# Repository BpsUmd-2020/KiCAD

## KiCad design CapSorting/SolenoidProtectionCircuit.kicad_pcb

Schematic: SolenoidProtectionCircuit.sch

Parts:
D1, D12: 1N4003; D_DO-41_SOD81_P10.16mm_Horizontal
J11: Conn_01x06; JST_XH_S6B-XH-A_1x06_P2.50mm_Horizontal
Q1, Q12: 2SA1015; TO-92_Inline
Q2, Q13: IRLB8721PBF; IRLB8721PBF-2
R1, R3, R12, R14: 10k; R_0603_1608Metric
R2, R13: 47k; R_0603_1608Metric
R4, R15: 22k; R_0603_1608Metric

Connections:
+24V: D1.1, D12.1, J11.6, Q1.1, Q12.1, R2.1, R13.1
GND: J11.1, Q2.3, Q13.3, R4.2, R15.2
unnamed: Q1.2, R3.2
unnamed: Q1.3, R1.1, R2.2
unnamed: Q2.1, R3.1, R4.1
unnamed: Q12.2, R14.2
unnamed: Q12.3, R12.1, R13.2
unnamed: Q13.1, R14.1, R15.1
PLC_Y006: J11.3, R12.2
PLC_Y012: J11.5, R1.2
Solenoid1: D12.2, J11.2, Q13.2
Solenoid2: D1.2, J11.4, Q2.2

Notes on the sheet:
Solenoid protection
Vgs:16.5V
Vds:30V Pd:65W(temp=25) 33W(temp=100)

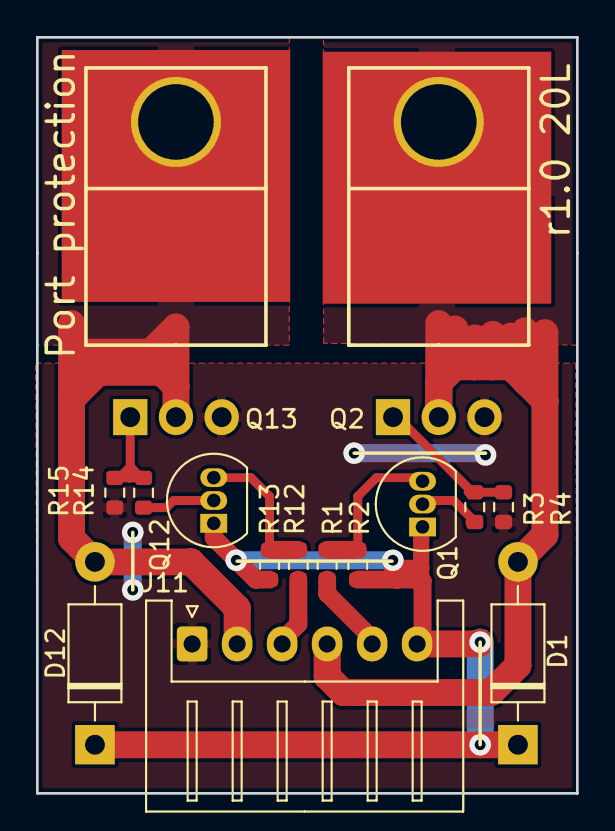
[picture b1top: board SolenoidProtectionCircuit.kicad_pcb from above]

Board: 2 copper layers, 30.0 x 42.0 mm, 15 parts (0 on the bottom side), 12 nets.

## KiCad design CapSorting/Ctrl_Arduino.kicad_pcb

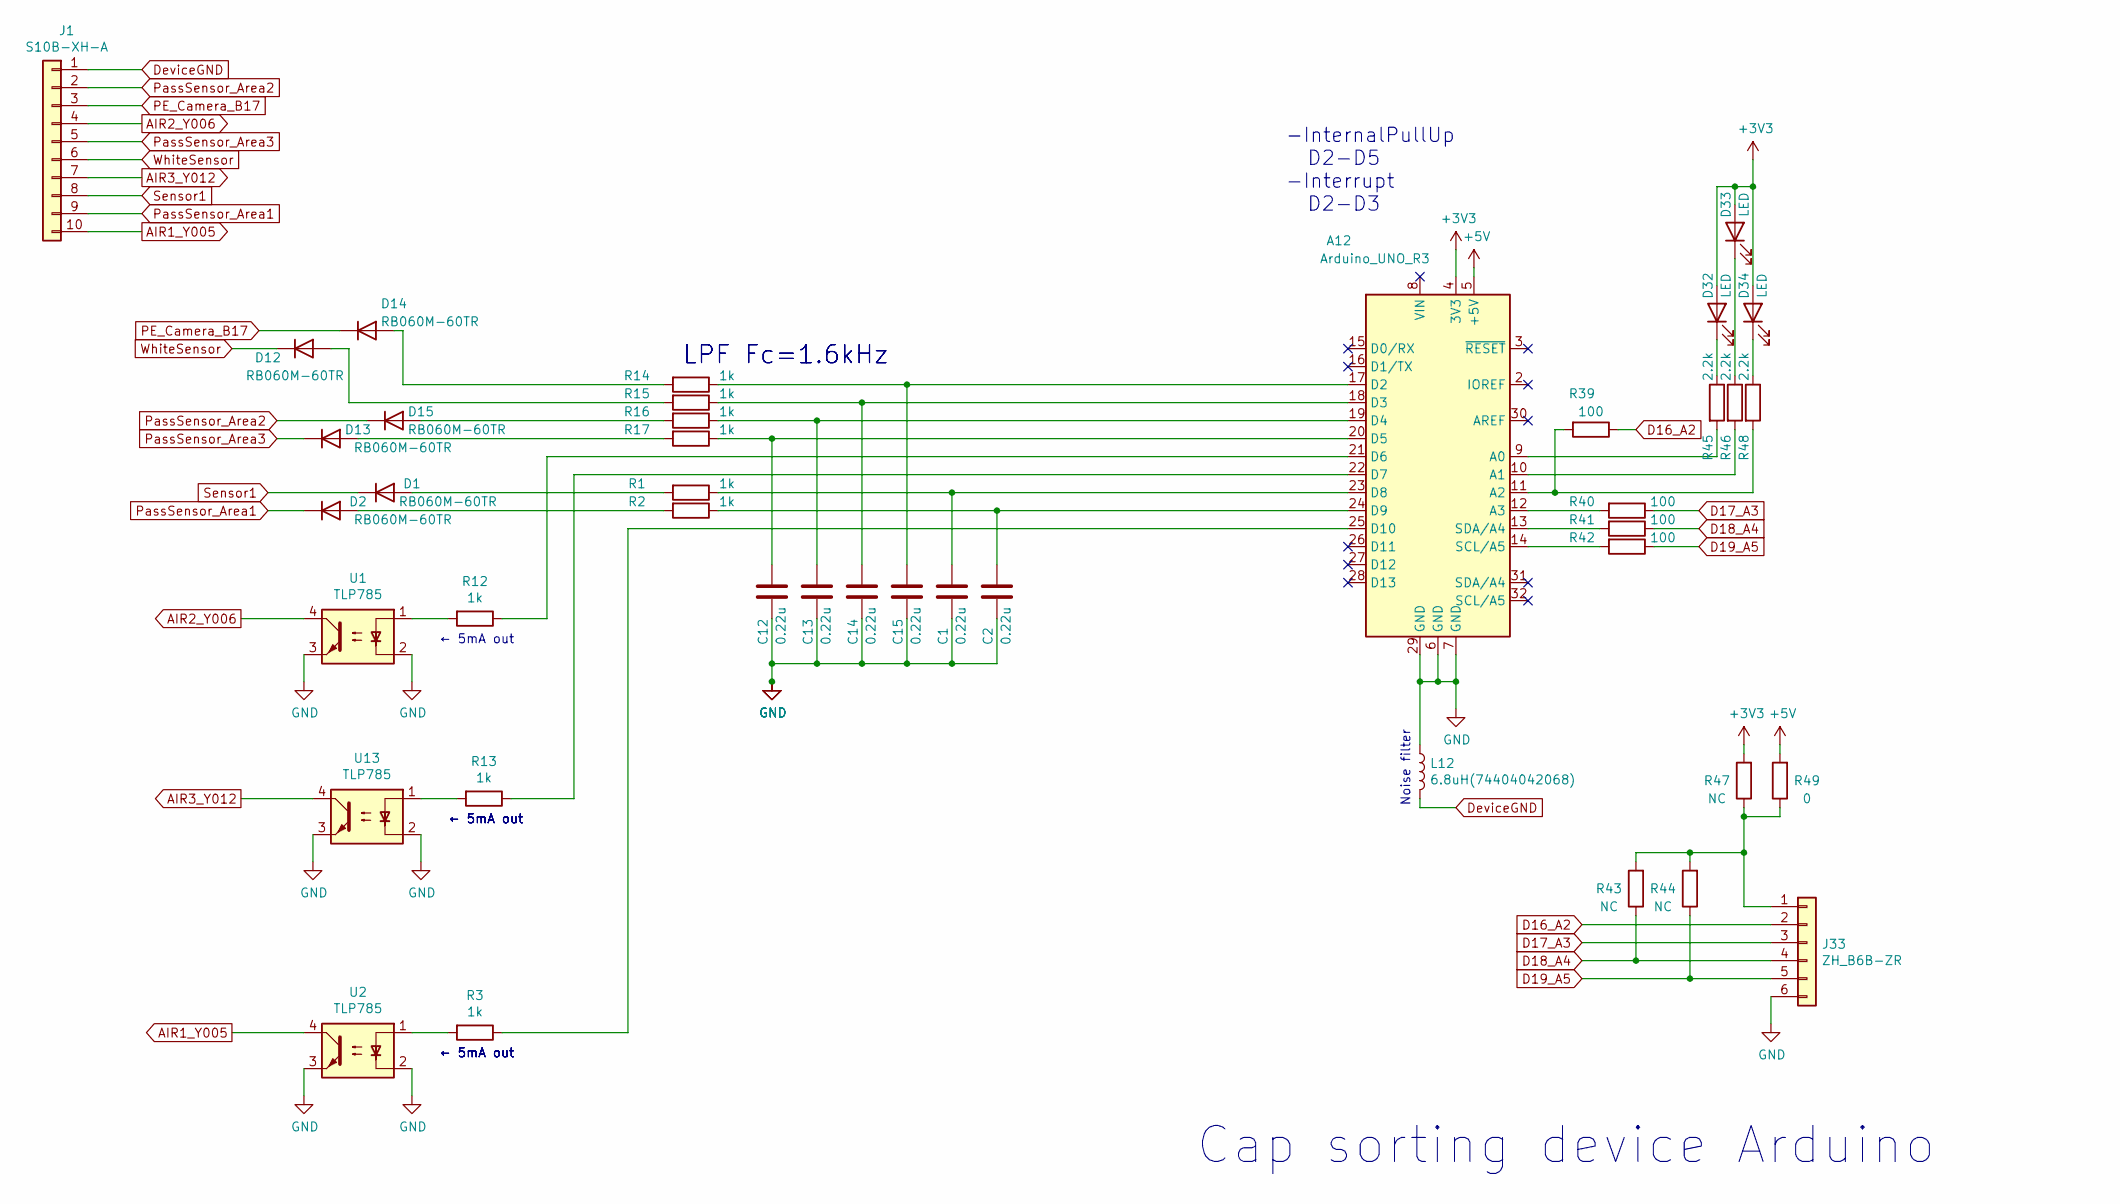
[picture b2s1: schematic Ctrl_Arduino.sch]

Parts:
A12: Arduino_UNO_R3; Arduino_UNO_R2
C1, C2, C12, C13, C14, C15: 0.22u; R_0402_1005Metric
D1, D2, D12, D13, D14, D15: RB060M-60TR; D_1206_3216Metric
D32, D33, D34: LED; LED1608
J1: S10B-XH-A; JST_XH_S10B-XH-A_1x10_P2.50mm_Horizontal
J33: ZH_B6B-ZR
L12: 6.8uH(74404042068); INDPM4040X180N
R1, R2, R3, R12, R13, R14, R15, R16, R17: 1k; R_0603_1608Metric
R39, R40, R41, R42: 100; R_0603_1608Metric
R43, R44, R47: NC; R_0603_1608Metric
R45, R46, R48: 2.2k; R_0603_1608Metric
R49: 0; R_0603_1608Metric
U1, U2, U13: TLP785; DIP-4_W7.62mm

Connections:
+3V3: A12.4 (3V3), D32.2 (A), D33.2 (A), D34.2 (A), R47.2
+5V: A12.5 (+5V), R49.2
AIR1_Y005: J1.10, U2.4
AIR2_Y006: J1.4, U1.4
AIR3_Y012: J1.7, U13.4
D16_A2: J33.2, R39.1
D17_A3: J33.3, R40.1
D18_A4: J33.4, R41.1, R43.1
D19_A5: J33.5, R42.1, R44.1
DeviceGND: J1.1, L12.2
GND: A12.6 (GND), A12.7 (GND), A12.29 (GND), C1.2, C2.2, C12.2, C13.2, C14.2, C15.2, J33.6, L12.1, U1.2, U1.3, U2.2, U2.3, U13.2, U13.3
unnamed: A12.9 (A0), R45.2
unnamed: A12.10 (A1), R46.2
unnamed: A12.11 (A2), R39.2, R48.2
unnamed: A12.12 (A3), R40.2
unnamed: A12.13 (SDA/A4), R41.2
unnamed: A12.14 (SCL/A5), R42.2
unnamed: A12.17 (D2), C15.1, R14.1
unnamed: A12.18 (D3), C14.1, R15.1
unnamed: A12.19 (D4), C13.1, R16.1
unnamed: A12.20 (D5), C12.1, R17.1
unnamed: A12.21 (D6), R12.1
unnamed: A12.22 (D7), R13.1
unnamed: A12.23 (D8), C1.1, R1.1
unnamed: A12.24 (D9), C2.1, R2.1
unnamed: A12.25 (D10), R3.1
unnamed: D1.2 (A), R1.2
unnamed: D2.2 (A), R2.2
unnamed: D12.2 (A), R15.2
unnamed: D13.2 (A), R17.2
unnamed: D14.2 (A), R14.2
unnamed: D15.2 (A), R16.2
unnamed: D32.1 (K), R45.1
unnamed: D33.1 (K), R46.1
unnamed: D34.1 (K), R48.1
unnamed: J33.1, R43.2, R44.2, R47.1, R49.1
unnamed: R3.2, U2.1
unnamed: R12.2, U1.1
unnamed: R13.2, U13.1
PE_Camera_B17: D14.1 (K), J1.3
PassSensor_Area1: D2.1 (K), J1.9
PassSensor_Area2: D15.1 (K), J1.2
PassSensor_Area3: D13.1 (K), J1.5
Sensor1: D1.1 (K), J1.8
WhiteSensor: D12.1 (K), J1.6

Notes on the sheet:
LPF Fc=1.6kHz
← 5mA out
Noise filter
Cap sorting device Arduino
-InternalPullUp D2-D5 -Interrupt D2-D3

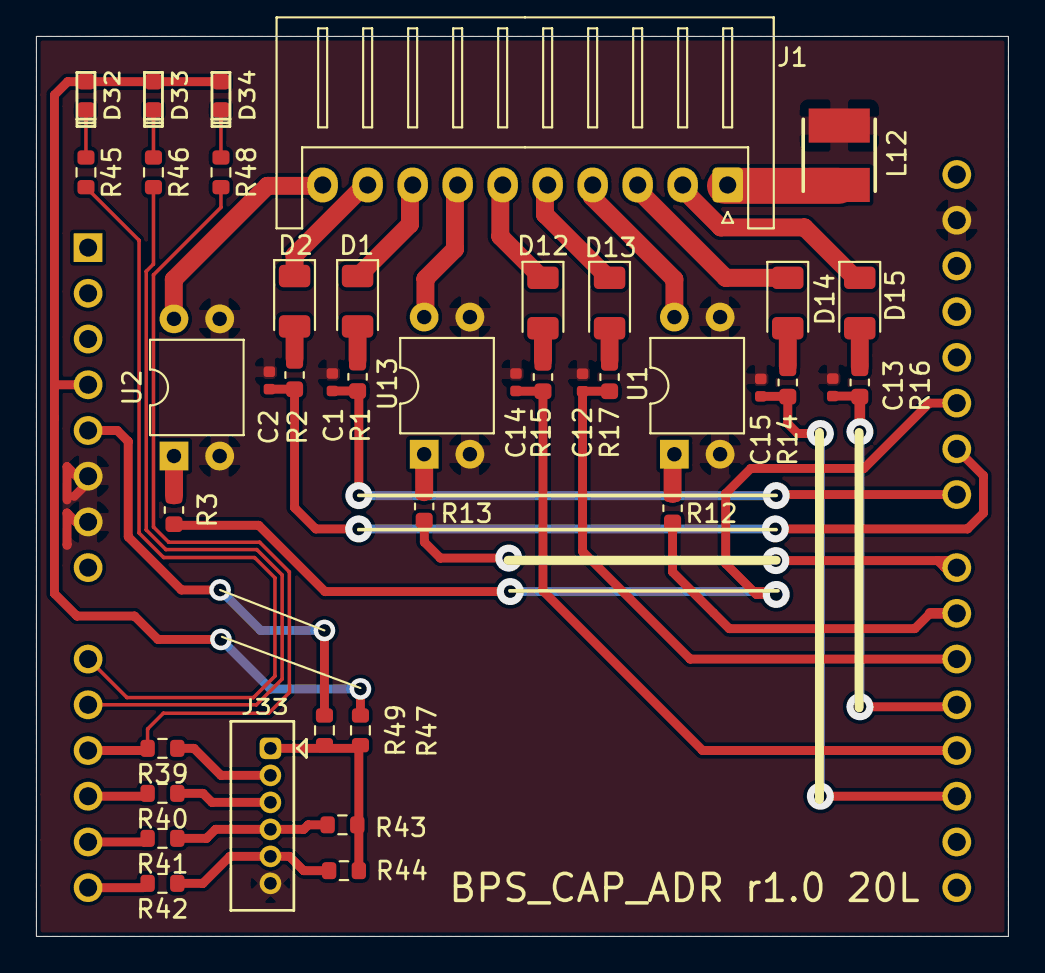
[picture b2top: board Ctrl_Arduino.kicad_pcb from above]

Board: 2 copper layers, 54.0 x 50.0 mm, 42 parts (1 on the bottom side), 45 nets.

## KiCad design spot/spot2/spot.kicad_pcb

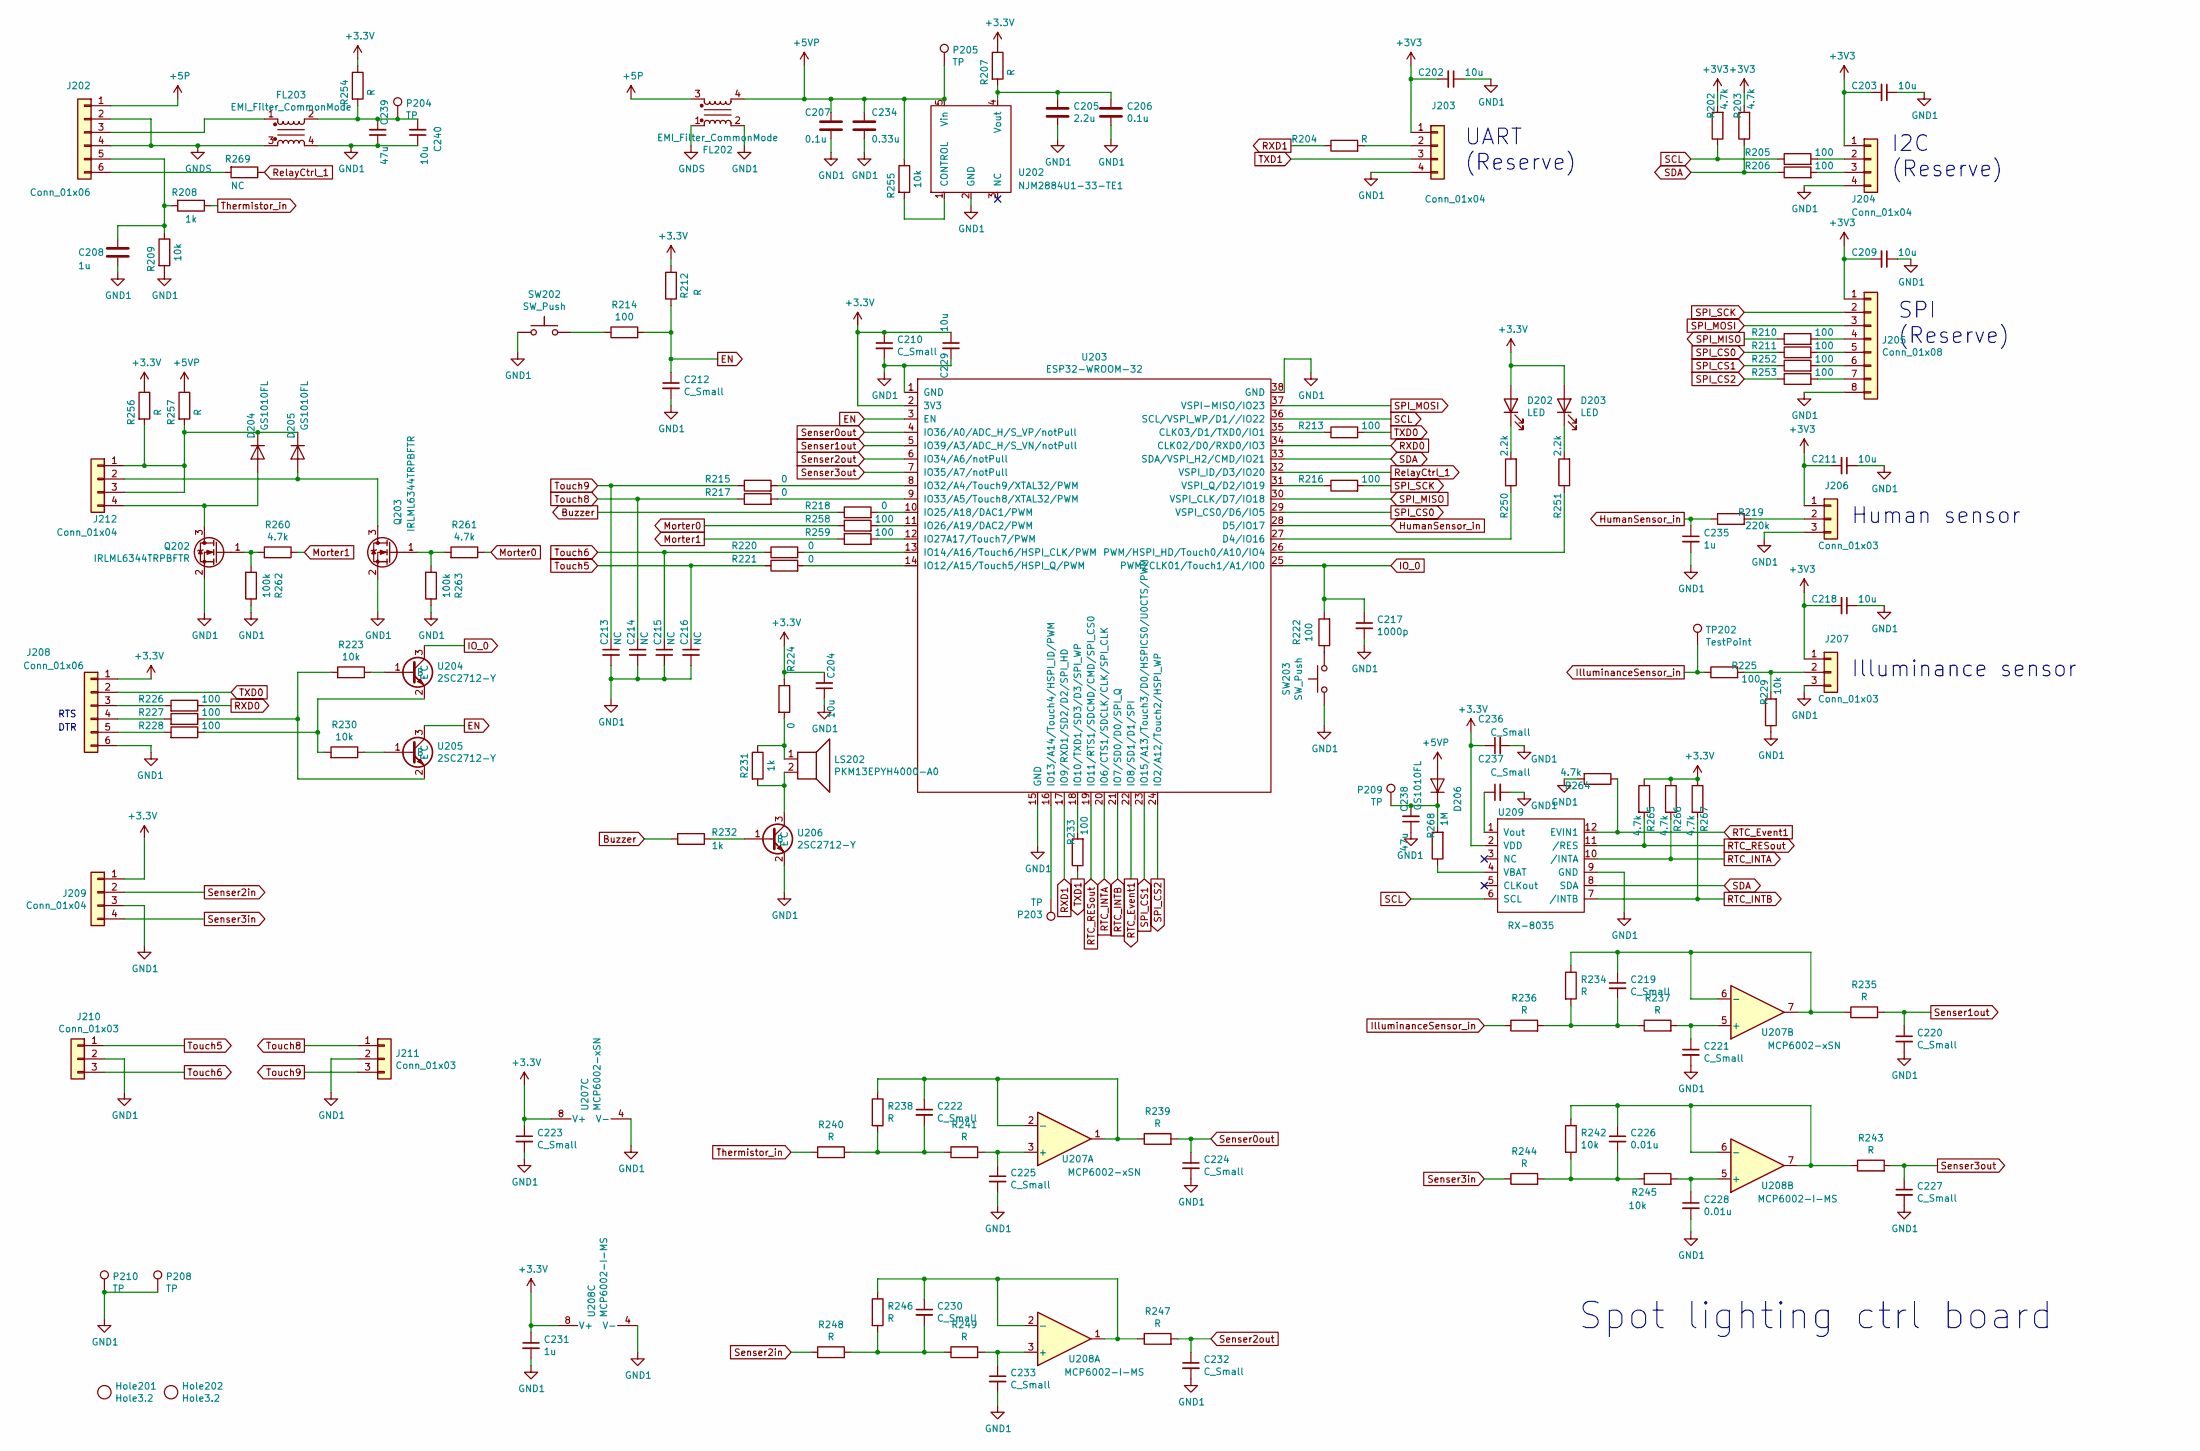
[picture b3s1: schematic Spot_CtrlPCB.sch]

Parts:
C202, C203, C204, C209, C211, C218, C229, C240: 10u; C_0603_1608Metric
C205: 2.2u; C_0805_2012Metric
C206, C207: 0.1u; C_0402_1005Metric
C208, C231, C235: 1u; C_0402_1005Metric
C210, C212, C219, C220, C221, C222, C223, C224, C225, C227, C230, C232, C233, C236, C237: C_Small; C_0402_1005Metric
C213, C214, C215, C216: NC; C_0402_1005Metric
C217: 1000p; C_0402_1005Metric
C226, C228: 0.01u; C_0402_1005Metric
C234: 0.33u; C_0603_1608Metric
C238, C239: 47u; C_1210_3225Metric
D202, D203: LED; LED1608
D204, D205, D206: GS1010FL
FL202, FL203: EMI_Filter_CommonMode; ACM2012-900-2P-T
Hole201, Hole202: Hole3.2
J202, J208: Conn_01x06; ZH_B6B-ZR
J203, J204, J209, J212: Conn_01x04; ZH_B4B-ZR
J205: Conn_01x08; ZH_B8B-ZR
J206, J207: Conn_01x03; ZH_B3B-ZR
J210, J211: Conn_01x03; PinHeader_1x03_P2.54mm_Vertical
LS202: PKM13EPYH4000-A0
P203, P204, P205, P208, P209, P210: TP; TP0.5
Q202, Q203: IRLML6344TRPBFTR
R202, R203, R260, R261, R264, R265, R266, R267: 4.7k; C_0402_1005Metric
R204, R212, R234, R235, R236, R237, R238, R239, R240, R241, R243, R244, R246, R247, R248, R249: R; C_0402_1005Metric
R205, R206, R210, R211, R213, R214, R216, R222, R225, R226, R227, R228, R233, R252, R253, R258, R259: 100; C_0402_1005Metric
R207, R254, R256, R257: R; C_0603_1608Metric
R208, R231, R232: 1k; C_0402_1005Metric
R209, R223, R229, R230, R242, R245, R255: 10k; C_0402_1005Metric
R215, R217, R218, R220, R221, R224: 0; C_0402_1005Metric
R219: 220k; C_0402_1005Metric
R250, R251: 2.2k; C_0402_1005Metric
R262, R263: 100k; C_0402_1005Metric
R268: 1M; C_0402_1005Metric
R269: NC; C_0402_1005Metric
SW202, SW203: SW_Push; TVAF06-A020B-R
TP202: TestPoint; TP0.5
U202: NJM2884U1-33-TE1
U203: ESP32-WROOM-32; ESP32-WROOM-32D
U204, U205, U206: 2SC2712-Y
U207: MCP6002-xSN; MCP6002-I-MS
U208: MCP6002-I-MS
U209: RX-8035

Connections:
+5P: FL202.3, J202.1
+5VP: C207.1, C234.1, D206.A, FL202.4, P205.1, R255.1, R257.1, U202.5 (Vin)
Buzzer: R218.1, R232.2
EN: C212.1, R212.1, R214.2, U203.3 (EN), U205.3 (C)
GND1: C202.1, C203.1, C204.1, C205.2, C206.2, C207.2, C208.2, C209.1, C210.2, C211.1, C212.2, C213.2, C214.2, C215.2, C216.2, C217.2, C218.1, C220.2, C221.2, C223.2, C224.2, C225.2, C227.2, C228.2, C229.2, C231.2, C232.2, C233.2, C234.2, C235.2, C236.2, C237.2, C238.1, C239.1, C240.1, FL202.2, FL203.4, J203.4, J204.4, J205.8, J206.3, J207.3, J208.6, J209.3, J210.2, J211.2, P208.1, P210.1, Q202.2 (S), Q203.2 (S), R209.2, R229.1, R262.1, R263.1, R264.2, SW202.1, SW203.1, U202.2 (GND), U203.1 (GND), U203.15 (GND), U203.38 (GND), U206.2 (E), U207.4 (V-), U208.4 (V-), U209.9 (GND)
GNDS: FL202.1, FL203.3, J202.2, J202.4
HumanSensor_in: C235.1, R219.1, U203.28 (D5/IO17)
IO_0: C217.1, R222.2, U203.25 (PWM/CLK01/Touch1/A1/IO0), U204.3 (C)
IlluminanceSensor_in: R225.1, R236.1, TP202.1
Morter0: R258.1, R261.1
Morter1: R259.1, R260.1
unnamed: C205.1, C206.1, R207.2, U202.4 (Vout)
unnamed: C208.1, J202.5, R208.2, R209.1
unnamed: C219.1, R234.1, R235.1, U207.6 (-), U207.7
unnamed: C219.2, R234.2, R236.2, R237.1
unnamed: C221.1, R237.2, U207.5 (+)
unnamed: C222.1, R238.1, R239.1, U207.1, U207.2 (-)
unnamed: C222.2, R238.2, R240.2, R241.1
unnamed: C225.1, R241.2, U207.3 (+)
unnamed: C226.1, R242.1, R243.1, U208.6 (-), U208.7
unnamed: C226.2, R242.2, R244.2, R245.1
unnamed: C228.1, R245.2, U208.5 (+)
unnamed: C230.1, R246.1, R247.1, U208.1, U208.2 (-)
unnamed: C230.2, R246.2, R248.2, R249.1
unnamed: C233.1, R249.2, U208.3 (+)
unnamed: C237.1, U209.1 (Vout)
unnamed: C238.2, D206.K, P209.1, R268.2
unnamed: C239.2, C240.2, FL203.2, P204.1, R254.2
unnamed: D202.1 (K), R250.2
unnamed: D203.1 (K), R251.2
unnamed: D204.A, J212.4, Q202.3 (D)
unnamed: D204.K, D205.K, J212.1, J212.3, R256.2, R257.2
unnamed: D205.A, J212.2, Q203.3 (D)
unnamed: FL203.1, J202.3
unnamed: J202.6, R269.2
unnamed: J203.2, R204.2
unnamed: J204.2, R205.2
unnamed: J204.3, R206.2
unnamed: J205.4, R210.2
unnamed: J205.5, R211.2
unnamed: J205.6, R252.2
unnamed: J205.7, R253.2
unnamed: J206.2, R219.2
unnamed: J207.2, R225.2, R229.2
unnamed: J208.3, R226.2
unnamed: J208.4, R227.2
unnamed: J208.5, R228.2
unnamed: LS202.1, R224.2, R231.1
unnamed: LS202.2, R231.2, U206.3 (C)
unnamed: P203.1, U203.16 (IO13/A14/Touch4/HSPI_ID/PWM)
unnamed: Q202.1 (G), R260.2, R262.2
unnamed: Q203.1 (G), R261.2, R263.2
unnamed: R213.1, U203.35 (CLK03/D1/TXD0/IO1)
unnamed: R214.1, SW202.2
unnamed: R215.2, U203.8 (IO32/A4/Touch9/XTAL32/PWM)
unnamed: R216.1, U203.31 (VSPI_Q/D2/IO19)
unnamed: R217.2, U203.9 (IO33/A5/Touch8/XTAL32/PWM)
unnamed: R218.2, U203.10 (IO25/A18/DAC1/PWM)
unnamed: R220.2, U203.13 (IO14/A16/Touch6/HSPI_CLK/PWM)
unnamed: R221.2, U203.14 (IO12/A15/Touch5/HSPI_Q/PWM)
unnamed: R222.1, SW203.2
unnamed: R223.1, U204.1 (B)
unnamed: R223.2, R227.1, U205.2 (E)
unnamed: R228.1, R230.2, U204.2 (E)
unnamed: R230.1, U205.1 (B)
unnamed: R232.1, U206.1 (B)
unnamed: R233.2, U203.18 (IO10/TXD1/SD3/D3/SPI_WP)
unnamed: R250.1, U203.27 (D4/IO16)
unnamed: R251.1, U203.26 (PWM/HSPI_HD/Touch0/A10/IO4)
unnamed: R255.2, U202.1 (CONTROL)
unnamed: R258.2, U203.11 (IO26/A19/DAC2/PWM)
unnamed: R259.2, U203.12 (IO27A17/Touch7/PWM)
unnamed: R268.1, U209.4 (VBAT)
RTC_Event1: R264.1, U203.22 (IO8/SD1/D1/SPI), U209.12 (EVIN1)
RTC_INTA: R266.2, U203.20 (IO6/CTS1/SDCLK/CLK/SPI_CLK), U209.10 (/INTA)
RTC_INTB: R267.2, U203.21 (IO7/SD0/D0/SPI_Q), U209.7 (/INTB)
RTC_RESout: R265.2, U203.19 (IO11/RTS1/SDCMD/CMD/SPI_CS0), U209.11 (/RES)
RXD0: R226.1, U203.34 (CLK02/D0/RXD0/IO3)
RXD1: R204.1, U203.17 (IO9/RXD1/SD2/D2/SPI_HD)
RelayCtrl_1: R269.1, U203.32 (VSPI_ID/D3/IO20)
SCL: R202.1, R205.1, U203.36 (SCL/VSPI_WP/D1//IO22), U209.6 (SCL)
SDA: R203.1, R206.1, U203.33 (SDA/VSPI_H2/CMD/IO21), U209.8 (SDA)
SPI_CS0: R211.1, U203.29 (VSPI_CS0/D6/IO5)
SPI_CS1: R252.1, U203.23 (IO15/A13/Touch3/D0/HSPICS0/U0CTS/PWM)
SPI_CS2: R253.1, U203.24 (IO2/A12/Touch2/HSPI_WP)
SPI_MISO: R210.1, U203.30 (VSPI_CLK/D7/IO18)
SPI_MOSI: J205.3, U203.37 (VSPI-MISO/IO23)
SPI_SCK: J205.2, R216.2
Senser0out: C224.1, R239.2, U203.4 (IO36/A0/ADC_H/S_VP/notPull)
Senser1out: C220.1, R235.2, U203.5 (IO39/A3/ADC_H/S_VN/notPull)
Senser2in: J209.2, R248.1
Senser2out: C232.1, R247.2, U203.6 (IO34/A6/notPull)
Senser3in: J209.4, R244.1
Senser3out: C227.1, R243.2, U203.7 (IO35/A7/notPull)
TXD0: J208.2, R213.2
TXD1: J203.3, R233.1
Thermistor_in: R208.1, R240.1
Touch5: C216.1, J210.1, R221.1
Touch6: C215.1, J210.3, R220.1
Touch8: C214.1, J211.1, R217.1
Touch9: C213.1, J211.3, R215.1

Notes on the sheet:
Spot lighting ctrl board
I2C (Reserve)
UART (Reserve)
Illuminance sensor
Human sensor
SPI (Reserve)
DTR
RTS

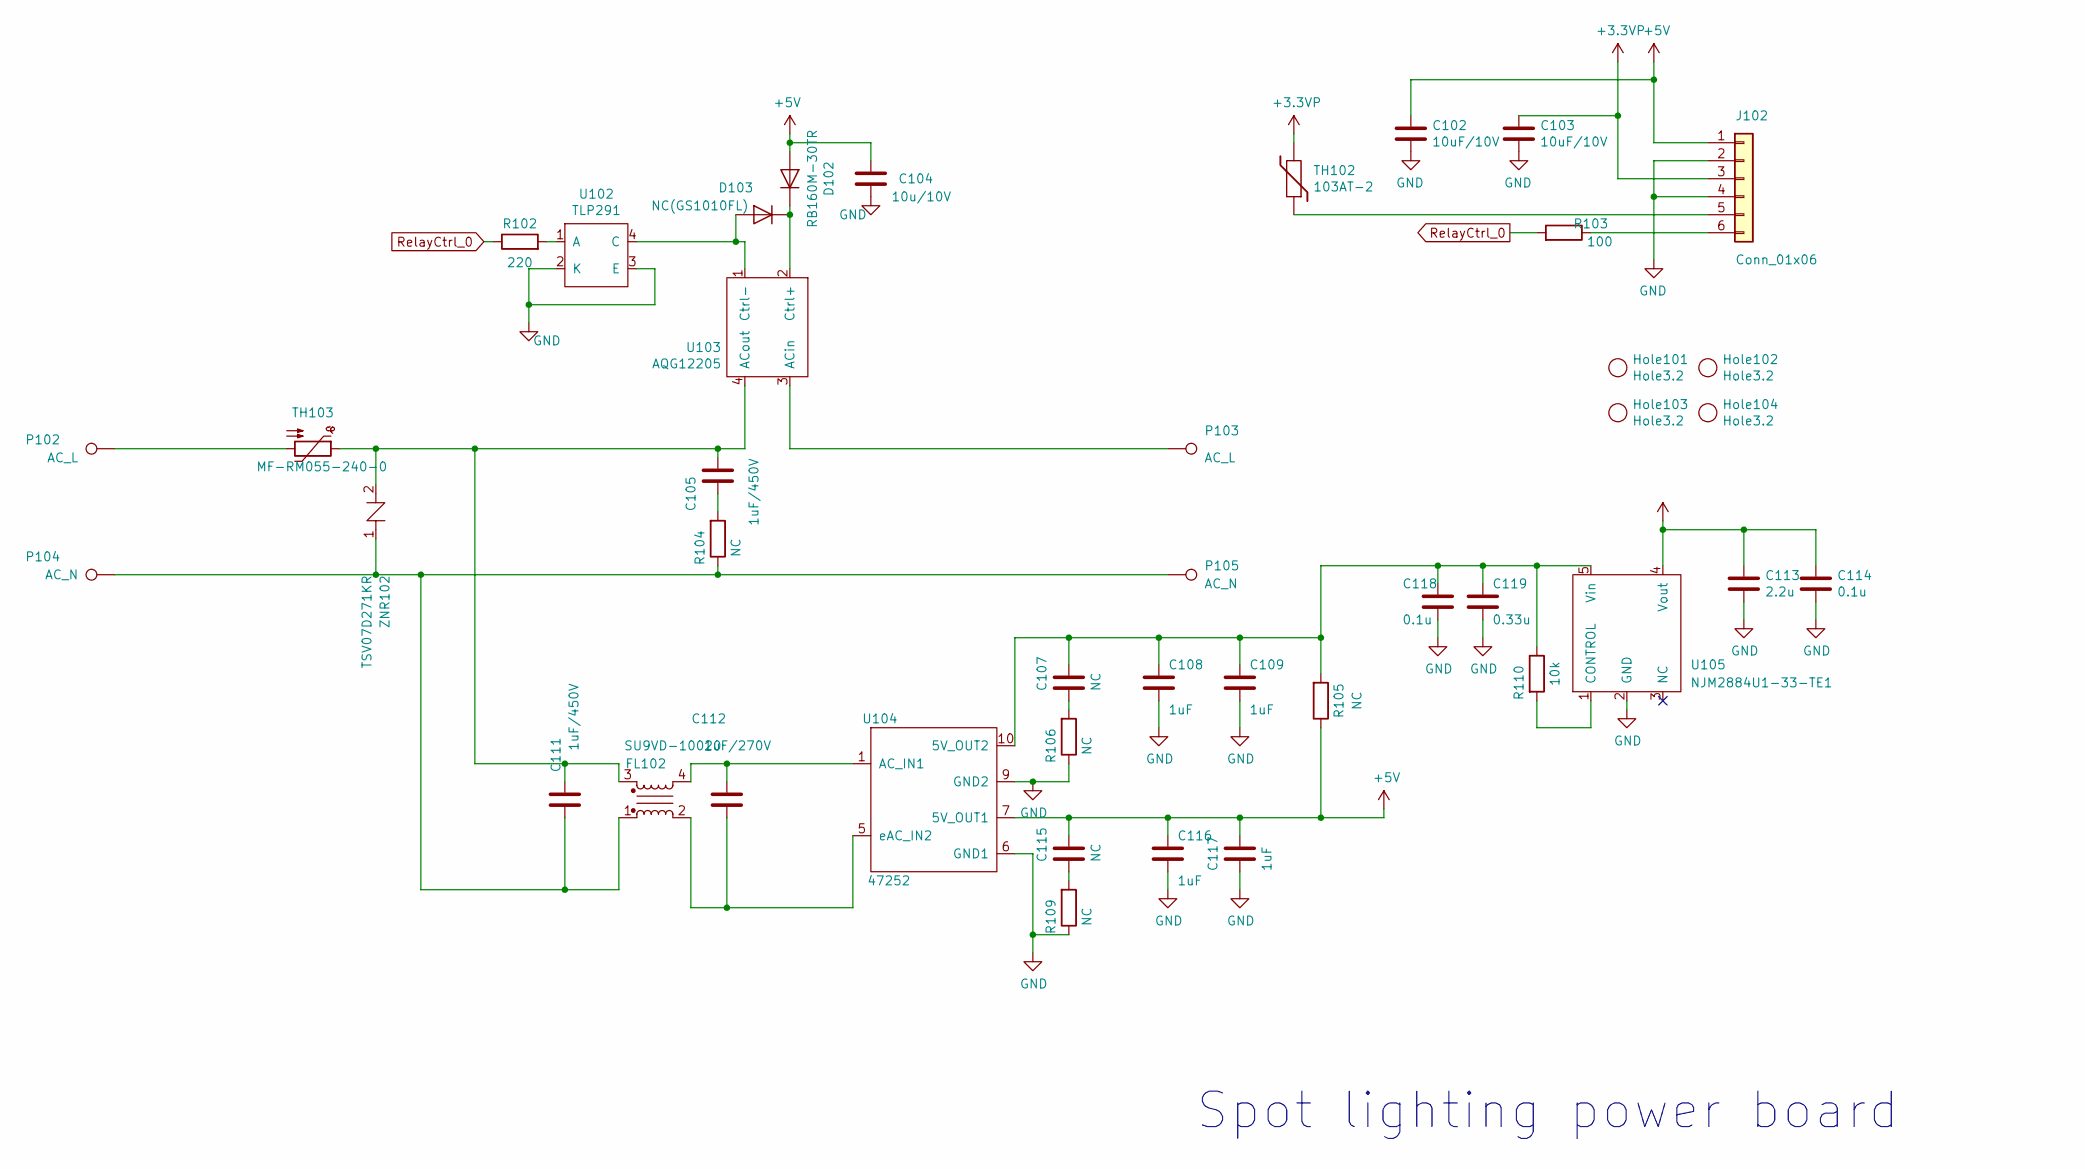
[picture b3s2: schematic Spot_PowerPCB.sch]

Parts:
C102, C103: 10uF/10V; C_0603_1608Metric
C104: 10u/10V; C_0603_1608Metric
C105, C111: 1uF/450V; ECQE2105KF
C107, C115: NC; C_0402_1005Metric
C108, C116: 1uF; C_1210_3225Metric
C109, C117: 1uF; C_0402_1005Metric
C112: 1uF/270V; ECQE2105KF
C113: 2.2u; C_0805_2012Metric
C114, C118: 0.1u; C_0402_1005Metric
C119: 0.33u; C_0603_1608Metric
D102: RB160M-30TR; RB168M-40TR
D103: NC(GS1010FL); GS1010FL
FL102: SU9VD-10020
Hole101, Hole102, Hole103, Hole104: Hole3.2
J102: Conn_01x06; ZH_B6B-ZR
P102, P103: AC_L; AC-TP
P104, P105: AC_N; AC-TP
R102: 220; C_0402_1005Metric
R103: 100; C_0402_1005Metric
R104: NC; CFS50J1MB
R105: NC; C_0603_1608Metric
R106, R109: NC; C_0402_1005Metric
R110: 10k; C_0402_1005Metric
TH102: 103AT-2
TH103: MF-RM055-240-0
U102: TLP291
U103: AQG12205
U104: 47252
U105: NJM2884U1-33-TE1
ZNR102: TSV07D271KR

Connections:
+3.3VP: C103.1, C113.1, C114.1, J102.3, TH102.2, U105.4 (Vout)
+5V: C102.1, C104.1, C115.1, C116.1, C117.1, D102.A, J102.1, R105.1, U104.7 (5V_OUT1)
GND: C102.2, C103.2, C104.2, C108.2, C109.2, C113.2, C114.2, C116.2, C117.2, C118.2, C119.2, J102.2, J102.4, R106.1, R109.1, U102.2 (K), U102.3 (E), U104.6 (GND1), U104.9 (GND2), U105.2 (GND)
unnamed: C105.1, R104.2
unnamed: C105.2, C111.2, FL102.3, TH103.1, U103.4 (ACout), ZNR102.2
unnamed: C107.1, C108.1, C109.1, C118.1, C119.1, R105.2, R110.1, U104.10 (5V_OUT2), U105.5 (Vin)
unnamed: C107.2, R106.2
unnamed: C111.1, FL102.1, P104.1, P105.1, R104.1, ZNR102.1
unnamed: C112.1, FL102.2, U104.5 (eAC_IN2)
unnamed: C112.2, FL102.4, U104.1 (AC_IN1)
unnamed: C115.2, R109.2
unnamed: D102.K, D103.K, U103.2 (Ctrl+)
unnamed: D103.A, U102.4 (C), U103.1 (Ctrl-)
unnamed: J102.5, TH102.1
unnamed: J102.6, R103.1
unnamed: P102.1, TH103.2
unnamed: P103.1, U103.3 (ACin)
unnamed: R102.2, U102.1 (A)
unnamed: R110.2, U105.1 (CONTROL)
RelayCtrl_0: R102.1, R103.2

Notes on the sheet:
Spot lighting power board

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
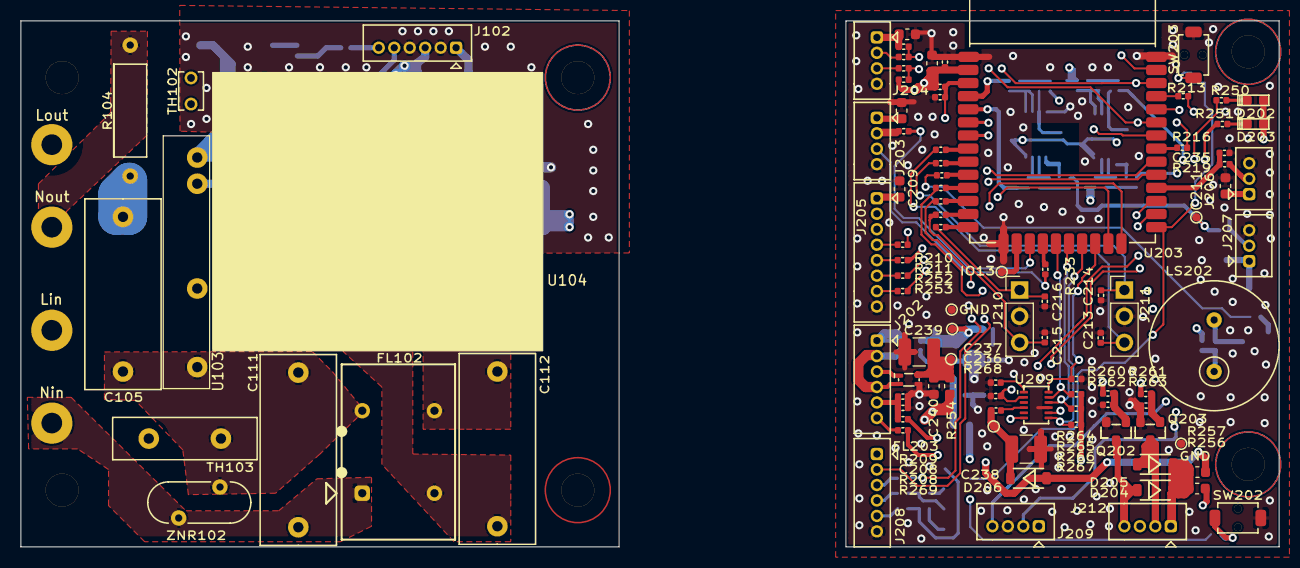
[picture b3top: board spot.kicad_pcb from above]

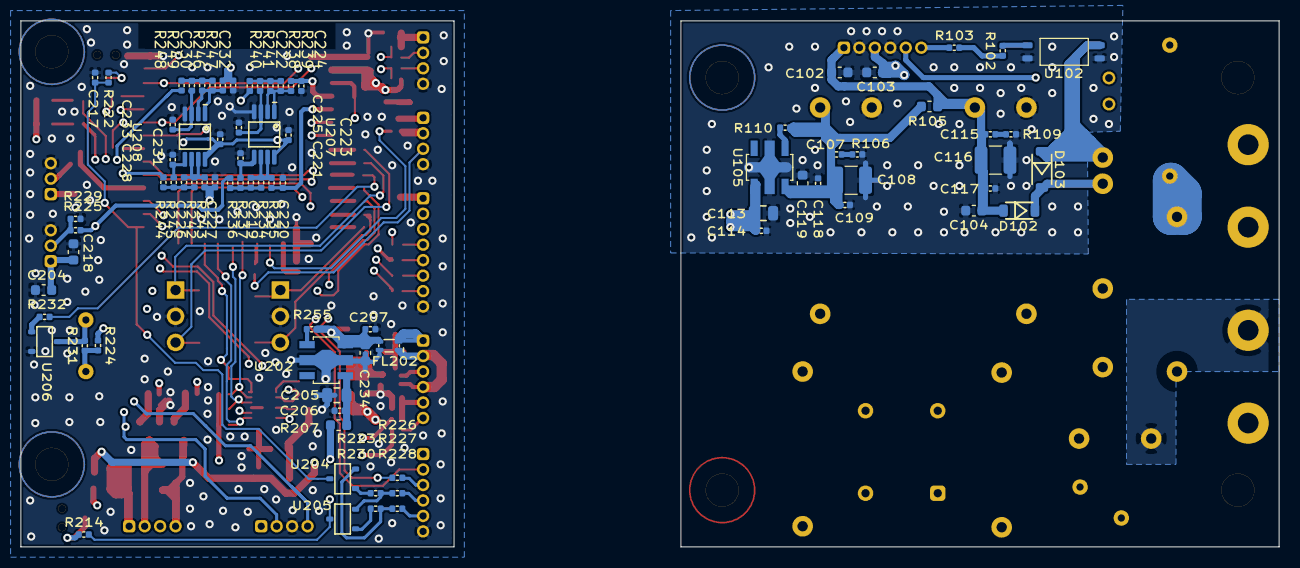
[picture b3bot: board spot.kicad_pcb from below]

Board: 4 copper layers, 122.0 x 51.0 mm, 189 parts (81 on the bottom side), 122 nets.

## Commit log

2020-12-23 Arduino回路図 コネクタ追加
2020-12-23 Android シール用追加
2020-12-24 no message
2020-12-25 引き直し
2020-12-25 ガーバデータ追加
2020-12-26 マスクデータ再編集したガーバデータを追加
2020-12-28 部品配置図
